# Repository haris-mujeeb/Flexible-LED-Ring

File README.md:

# 🌈 Flexible-LED-Ring: Ultra-Low-Power (ULP) Control System

A highly energy-efficient controller built around the **STM32L011F4U6TR** microcontroller, designed for long-term battery operation. This project demonstrates advanced **Ultra-Low-Power (ULP)** techniques by driving a variable-frequency LED whose rate is controlled by an analog voltage input (ADC), minimising average current draw.

## ⚡ Core Low-Power Architecture

The system achieves microamp-level consumption by spending the maximum possible time in deep sleep modes, delegating all timing tasks to autonomous, low-frequency peripherals.

| Feature | Low-Power Implementation | Power Rationale |
| :--- | :--- | :--- |
| **System Clock** | **MSI @ 4.2 MHz (Scale 3)** | Runs the core voltage at the lowest possible level ($\approx 1.2\text{ V}$) for maximum efficiency in **Run Mode** and fast processing upon wake-up. |
| **Deep Sleep Mode** | **Stop Mode** (0.54 µA with RAM retention) | CPU is halted while the **LPTIM** continues to run autonomously, managing the blinking schedule. |
| **Variable Timing** | **LPTIM (Low Power Timer)** | Replaces high-consumption `HAL_Delay()` with a hardware timer clocked by the $\mathbf{LSI}$ (Low-Speed Internal oscillator). |
| **LED Duty Cycle** | Fixed **15ms Pulse** | The LED is only briefly turned ON, drastically reducing the single largest current draw source. |
| **I/O Gating** | **ADC\_EN (PA7)** control | External circuitry (e.g., analog front-end) is powered ON **only** during the brief ADC conversion window, minimising external leakage. |

## ✨ Functionality

### LED Control:
* **Variable Blink Rate:** The LED blink frequency is dynamically adjusted based on the **ADC value** (0-4095).
* **Low Duty Cycle:** A fixed $\mathbf{5\text{ ms}}$ pulse ensures energy efficiency across all blink frequencies.
* **Deep Sleep Toggle:** The single external switch (SW1/WKUP1) is used to manage the MCU's power state.
    * **First Press:** Activates the system (blinking begins/resumes).
    * **Second Press:** Deactivates blinking, putting the system into **Standby Mode** ($\approx 0.23\text{ µA}$) until the next press.

### 🔌 Charging Mechanism:
* ⚡ Utilises pogo pins for easy connection and charging.
* 💡 Charging LEDs illuminate when the pogo pins are connected and the battery is charging, turning off once fully charged.

## 🔬 Validation and Tools

The power consumption profile was rigorously measured using the **Nordic Power Profiler Kit II (PPK II)** to validate the efficacy of the **Stop Mode** and **Standby Mode** routines.

https://github.com/user-attachments/assets/664f258f-f0d6-4ddf-a007-7cb5bbc9106d

## 💻 Code:
Using ST-Link via Serial Wire debug mode, the program can be flashed onto the  highly energy-efficient STM32L011F4U6TR Microcontroller.

https://github.com/user-attachments/assets/1e935329-2498-4105-b1bf-f483a7316e35

## Assembly:
The PCB can be folded into a ring as shown below:

**References:**
- For setting up SysTick properly: [see here](https://community.st.com/t5/stm32-mcus-embedded-software/i-know-sounds-dumb-but-how-do-you-configure-systick/td-p/377723)
- For setting up External Interrupts: [see here](https://deepbluembedded.com/stm32-external-interrupt-example-lab/)
- For setting up ADC: [see here](https://controllerstech.com/stm32-adc1-single-channel-polling-mode/)
- For power analysis: [see here](https://www.nordicsemi.com/Products/Development-hardware/Power-Profiler-Kit-2)
- For low-power core configuration (Scale 3, Stop Mode): See [STM32L011x4 Datasheet](https://www.st.com/resource/en/datasheet/stm32l011f4.pdf) and [RM0377 Reference Manual](https://www.st.com/resource/en/reference_manual/rm0377-ultralowpower-stm32l0x1-advanced-armbased-32bit-mcus-stmicroelectronics.pdf)

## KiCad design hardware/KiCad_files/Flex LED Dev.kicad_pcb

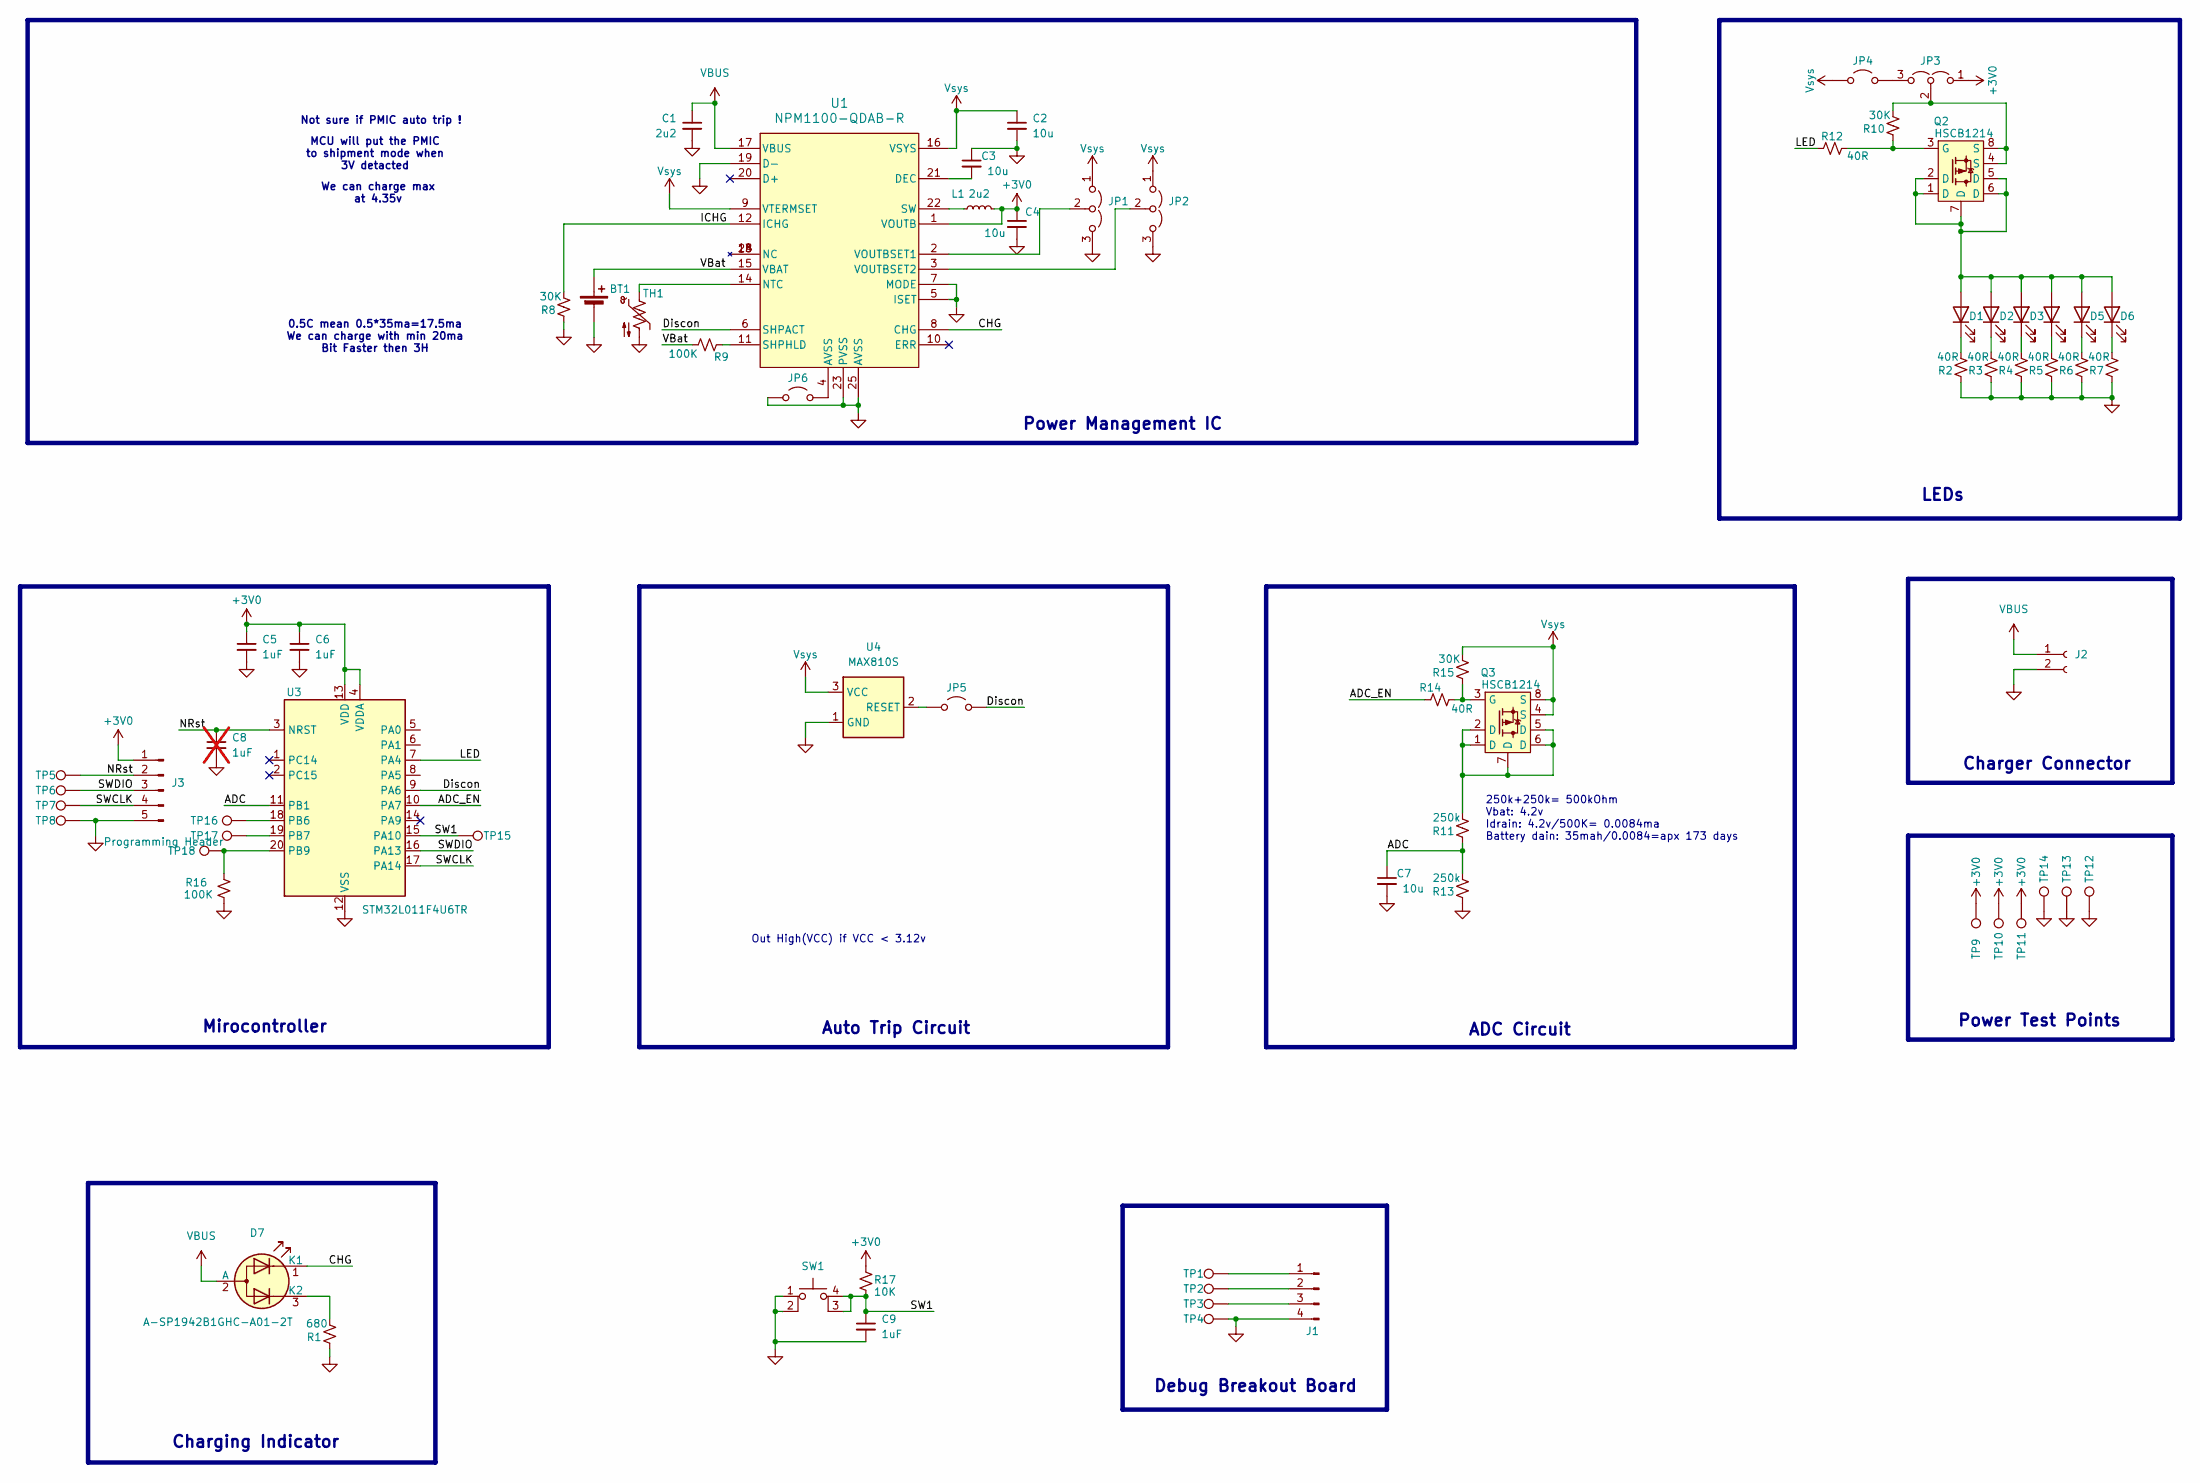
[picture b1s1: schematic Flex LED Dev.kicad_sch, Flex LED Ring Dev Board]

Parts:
BT1: ICB1040F6; C_0603_1608Metric
C1: 2u2; C_0402_1005Metric
C2, C3, C4, C7: 10u; C_0402_1005Metric
C5, C6: 1uF; C_0402_1005Metric
C8: 1uF; C_0402_1005Metric; not fitted
C9: 1uF; C_0402_1005Metric; Mfr. # CL05A105KA5NQNC; LCSC Part # C52923
D1, D2, D3, D4, D5, D6: LED_0805_2012Metric; Mfr. # APTD2012LSYCK; LCSC Part # C5588998
D7: A-SP1942B1GHC-A01-2T
J1: YZ165615055F-04025-01
J2: Charger Connector; TerminalBlock_Xinya_XY308-2.54-2P_1x02_P2.54mm_Horizontal
J3: Programming Header; PinHeader_1x05_P2.54mm_Vertical
JP1, JP2, JP3: 0402 Jumper; 3_Jump_0402
JP4, JP5, JP6: Jumper_2; Jumper_0402
L1: 2u2; L_0603_1608Metric; Mfr. Part # CIGT252008LM2R2MNE
Q2, Q3: HSCB1214
R1: 680; R_0402_1005Metric; Mfr. # RC0402FR-07820RL; LCSC Part # C137933
R2, R3, R4, R5, R6, R7, R12, R14: 40R; R_0402_1005Metric
R8, R10, R15: 30K; R_0402_1005Metric
R9, R16: 100K; R_0402_1005Metric
R11, R13: 250k; R_0402_1005Metric
R17: 10K; R_0402_1005Metric; Mfr. # RC0402FR-0710KL; LCSC Part # C60490
SW1: TS-1187A-B-A-B
TH1: NTCG103JF103FT1; C_0402_1005Metric
TP1, TP2, TP3, TP4: PH; PinHeader_1x01_P2.00mm_Vertical
TP5: PH; TestPoint_Pad_1.0x1.0mm
TP6, TP7, TP8, TP9, TP10, TP11, TP12, TP13, TP14, TP15, TP16, TP17, TP18: PH; TestPoint_Pad_D1.0mm
U1: NPM1100-QDAB-R; QFN-24-1EP_4x4mm_P0.5mm_EP2.7x2.7mm; Mfr. Part # NPM1100-QDAA-R; LCSC Part # C5816773
U3: STM32L011F4U6TR; ST_UFQFPN-20_3x3mm_P0.5mm
U4: MAX810S; SOT-23-3

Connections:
+3V0: C4.1, C5.1, C6.1, J3.1, JP3.1 (A), L1.2, R17.1, TP9.1, TP10.1, TP11.1, U1.1 (VOUTB), U3.4 (VDDA), U3.13 (VDD)
/ADC: C7.1, R11.1, R13.2, U3.11 (PB1)
/ADC_EN: R14.2, U3.10 (PA7)
/CHG: D7.1 (K1), U1.8 (CHG)
/Discon: JP5.2 (B), U1.6 (SHPACT), U3.9 (PA6)
/ICHG: R8.2, U1.12 (ICHG)
/LED: R12.2, U3.7 (PA4)
/NRst: C8.1, J3.2, TP5.1, U3.3 (NRST)
/SW1: C9.1, R17.2, SW1.3 (K), SW1.4 (A), TP15.1, U3.15 (PA10)
/SWCLK: J3.4, TP7.1, U3.17 (PA14)
/SWDIO: J3.3, TP6.1, U3.16 (PA13)
/VBat: BT1.1 (+), R9.2, U1.15 (VBAT)
GND: BT1.2 (-), C1.2, C2.2, C3.1, C4.2, C5.2, C6.2, C7.2, C8.2, C9.2, J2.2, J3.5, JP1.3 (B), JP2.3 (B), JP6.1 (A), R1.1, R2.1, R3.1, R4.1, R5.1, R6.1, R7.1, R8.1, R13.1, R16.2, SW1.1, SW1.2, TH1.2, TP8.1, TP12.1, TP13.1, TP14.1, U1.5 (ISET), U1.7 (MODE), U1.19 (D-), U1.23 (PVSS), U1.25 (AVSS), U3.12 (VSS), U4.1 (GND)
GNDA: J1.4, TP4.1
unnamed: D1.2 (A), D2.2 (A), D3.2 (A), D4.2 (A), D5.2 (A), D6.2 (A), Q2.1 (D), Q2.2 (D), Q2.5 (D), Q2.6 (D), Q2.7 (D)
unnamed: D1.1 (K), R2.2
unnamed: D2.1 (K), R3.2
unnamed: D3.1 (K), R4.2
unnamed: D4.1 (K), R5.2
unnamed: D5.1 (K), R6.2
unnamed: D6.1 (K), R7.2
unnamed: D7.3 (K2), R1.2
unnamed: J1.1, TP1.1
unnamed: J1.2, TP2.1
unnamed: J1.3, TP3.1
unnamed: JP1.2 (C), U1.2 (VOUTBSET1)
unnamed: JP2.2 (C), U1.3 (VOUTBSET2)
unnamed: JP3.3 (B), JP4.2 (B)
unnamed: JP3.2 (C), Q2.4 (S), Q2.8 (S), R10.2
unnamed: JP5.1 (A), U4.2 (RESET)
unnamed: JP6.2 (B), U1.4 (AVSS)
unnamed: Q2.3 (G), R10.1, R12.1
unnamed: Q3.1 (D), Q3.2 (D), Q3.5 (D), Q3.6 (D), Q3.7 (D), R11.2
unnamed: Q3.3 (G), R14.1, R15.1
unnamed: C3.2, U1.21 (DEC)
unnamed: TH1.1, U1.14 (NTC)
unnamed: R9.1, U1.11 (SHPHLD)
unnamed: L1.1, U1.22 (SW)
unnamed: TP16.1, U3.18 (PB6)
unnamed: TP17.1, U3.19 (PB7)
unnamed: R16.1, TP18.1, U3.20 (PB9)
VBUS: C1.1, D7.2 (A), J2.1, U1.17 (VBUS)
Vsys: C2.1, JP1.1 (A), JP2.1 (A), JP4.1 (A), Q3.4 (S), Q3.8 (S), R15.2, U1.9 (VTERMSET), U1.16 (VSYS), U4.3 (VCC)

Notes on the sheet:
Not sure if PMIC auto trip !
Debug Breakout Board
Power Test Points
LEDs
Charging Indicator
Out High(VCC) if VCC < 3.12v
Power Management IC
0.5C mean 0.5*35ma=17.5ma We can charge with min 20ma Bit Faster then 3H
Auto Trip Circuit
ADC Circuit
250k+250k= 500kOhm Vbat: 4.2v Idrain: 4.2v/500K= 0.0084ma Battery dain: 35mah/0.0084=apx 173 days
Charger Connector
We can charge max at 4.35v
MCU will put the PMIC to shipment mode when 3V detacted
Mirocontroller

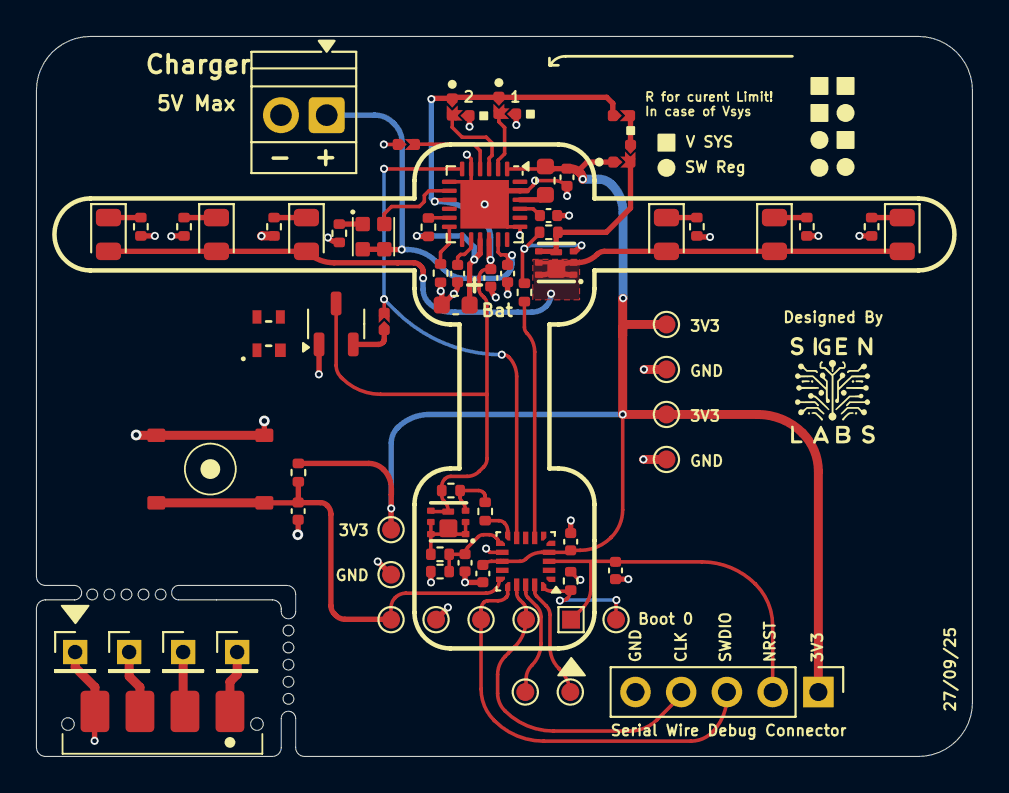
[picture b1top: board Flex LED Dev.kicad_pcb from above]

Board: 4 copper layers, 52.0 x 40.0 mm, 71 parts (0 on the bottom side), 43 nets.

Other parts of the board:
mouse-bite-1mm-slot, mouse-bite-1mm-slot#2: VAL**; mouse-bite-slot

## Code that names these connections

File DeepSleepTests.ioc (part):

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Mcu.Name=STM32L011F(3-4)Ux
Mcu.Package=UFQFPN20
Mcu.UserName=STM32L011F4Ux
PA0-CK_IN.GPIOParameters=GPIO_Label
PA0-CK_IN.GPIO_Label=ADC
PA0-CK_IN.Mode=IN0
PA0-CK_IN.Signal=ADC_IN0
PA13.Mode=Serial_Wire
PA13.Signal=SYS_SWDIO
PA14.Mode=Serial_Wire
PA14.Signal=SYS_SWCLK
PA4.GPIOParameters=GPIO_PuPd,GPIO_Label,GPIO_ModeDefaultOutputPP
PA4.GPIO_Label=LED
PA4.GPIO_ModeDefaultOutputPP=GPIO_MODE_OUTPUT_OD
PA4.GPIO_PuPd=GPIO_NOPULL
PA4.Signal=GPIO_Output
PA6.GPIOParameters=GPIO_Label
PA6.GPIO_Label=Discon
PA6.Signal=GPIO_Output
PA7.GPIOParameters=GPIO_PuPd,GPIO_Label,GPIO_ModeDefaultOutputPP
PA7.GPIO_Label=ADC_EN
PA7.GPIO_ModeDefaultOutputPP=GPIO_MODE_OUTPUT_OD
PA7.GPIO_PuPd=GPIO_NOPULL
PA7.Signal=GPIO_Output
PB1.GPIOParameters=GPIO_Label
PB1.GPIO_Label=WKUP1
PB1.Signal=GPXTI1
RCC.HSE_VALUE=8000000
RCC.SYSCLKFreq_VALUE=2097000
board=custom

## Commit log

2025-05-17 v0_1
2025-05-18 version 1.0
2025-05-27 set GPIO Ouput as Open-Drain
    The pin is configured as an open-drain output using GPIO_MODE_OUTPUT_OD. In this mode, the pin can pull the line low when set to RESET, but when set to SET, it does not drive the line high; instead, 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
2025-10-16 v2.0
